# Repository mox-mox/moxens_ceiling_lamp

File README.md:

moxens_ceiling_lamp
===================

This is the source to the lamp that is to light my room

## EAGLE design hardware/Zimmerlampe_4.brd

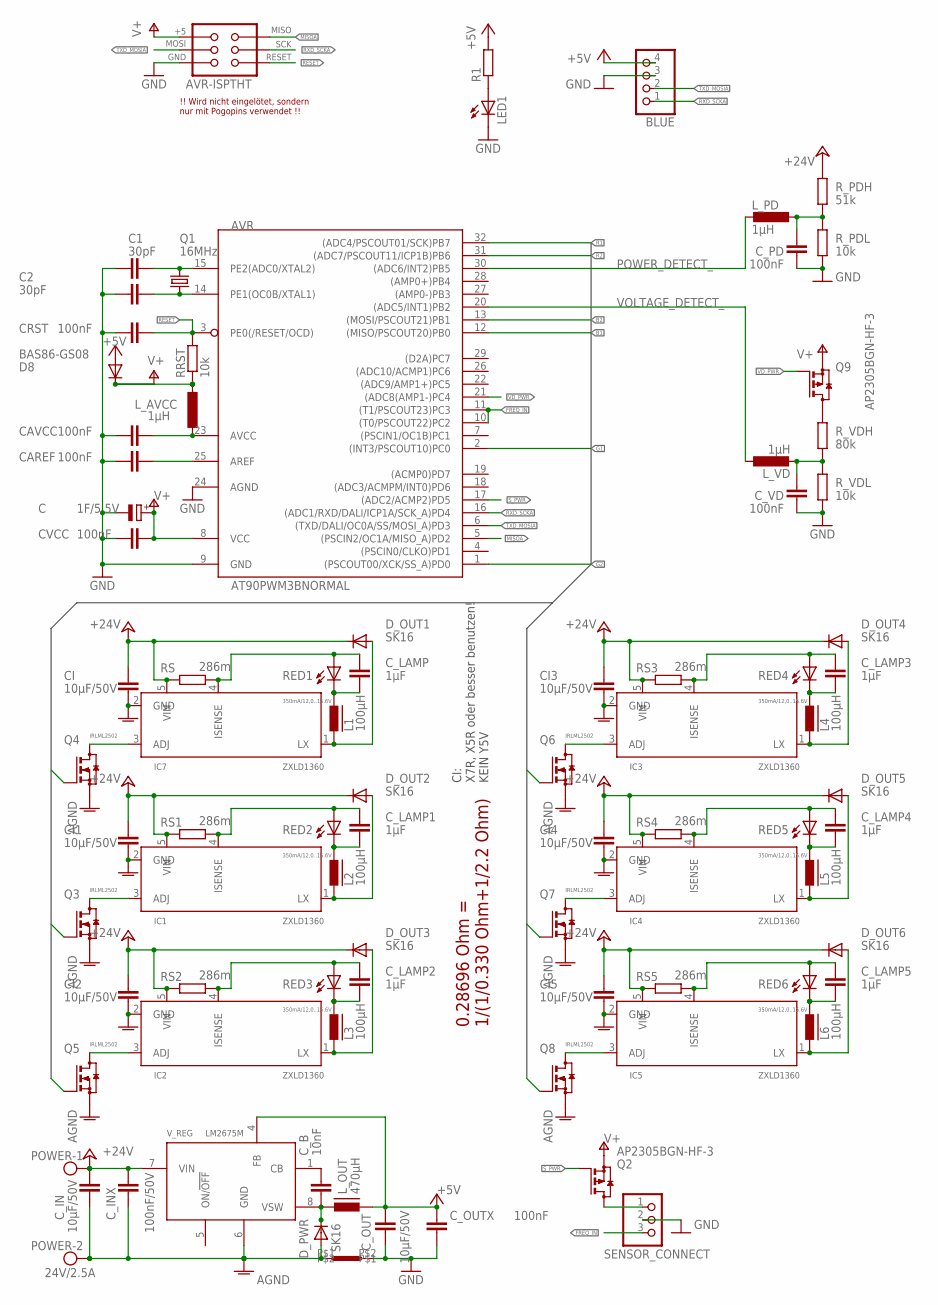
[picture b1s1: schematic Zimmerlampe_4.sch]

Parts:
AVR: AT90PWM3BNORMAL; SO32W
BLUE: PINHD-1X4_2.54-SMD-INLINE; 1X04SMD/INLINE
C: 1F/5.5V; PANASONIC_SG_TERMINAL_H
C1, C2: 30pF; C0805
CAREF: 100nF; C0805
CAVCC: 100nF; C0805
CI, CI1, CI2, CI3, CI4, CI5: 10µF/50V; C1210
CRST: 100nF; C0805
CVCC: 100nF; C0805
C_B: 10nF; C0805
C_IN: 10µF/50V; C1210
C_INX: 100nF/50V; C0805
C_LAMP, C_LAMP1, C_LAMP2, C_LAMP3, C_LAMP4, C_LAMP5: 1µF; C0805
C_OUT: 10µF/50V; C1210
C_OUTX: 100nF; C0805
C_PD: 100nF; C0805
C_VD: 100nF; C0805
D8: BAS86-GS08; MINIMELF
D_OUT1, D_OUT2, D_OUT3, D_OUT4, D_OUT5, D_OUT6: SK16; DO214AA
D_PWR: SK16; DO214AA
IC1, IC2, IC3, IC4, IC5, IC7: ZXLD1360; TSOT23-5
L1, L2, L3, L4, L5, L6: 100µH; FERROCORE_DER0705-
LED1: LEDSML0805; SML0805
L_AVCC: 1µH; L0805
L_OUT: 470µH; FERROCORE_DE1207-
L_PD: 1µH; L0805
L_VD: 1µH; L0805
POWER: 24V/2.5A; AK500/2
Q1: 16MHz; HC49UP
Q2, Q9: AP2305BGN-HF-3; SOT23
Q3, Q4, Q5, Q6, Q7, Q8: IRLML2502; SOT23
R1: R-EU_R0805; R0805
RED1, RED2: 350mA/12,0..15.6V; LED_CON_A
RED3, RED4, RED5, RED6: 350mA/12,0..15.6V; LED_CON_B
RRST: 10k; R0805
RS, RS1, RS2, RS3, RS4, RS5: 286m; R0805
R_PDH: 51k; R0805
R_PDL: 10k; R0805
R_VDH: 80k; R0805
R_VDL: 10k; R0805
SENSOR_CONNECT: 1X03SMD/INLINE
U$3: STARPOINT
U$7: AVR-ISPTHT; AVR-ISP-THT
V_REG: LM2675M; SO08

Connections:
+5V: BLUE.4, C_OUT.1, C_OUTX.1, D8.A, L_OUT.P$2 (2), R1.2, V_REG.4 (FB)
+24V: CI.1, CI1.1, CI2.1, CI3.1, CI4.1, CI5.1, C_IN.1, C_INX.1, D_OUT1.C, D_OUT2.C, D_OUT3.C, D_OUT4.C, D_OUT5.C, D_OUT6.C, IC1.5 (VIN), IC2.5 (VIN), IC3.5 (VIN), IC4.5 (VIN), IC5.5 (VIN), IC7.5 (VIN), POWER.1, RS.1, RS1.1, RS2.1, RS3.1, RS4.1, RS5.1, R_PDH.1, V_REG.7 (VIN)
ADJUST: IC7.3 (ADJ), Q4.3 (D)
ADJUST1: IC1.3 (ADJ), Q3.3 (D)
ADJUST2: IC2.3 (ADJ), Q5.3 (D)
ADJUST3: IC3.3 (ADJ), Q6.3 (D)
ADJUST4: IC4.3 (ADJ), Q7.3 (D)
ADJUST5: IC5.3 (ADJ), Q8.3 (D)
AGND: CI.2, CI1.2, CI2.2, CI3.2, CI4.2, CI5.2, C_IN.2, C_INX.2, D_PWR.A, IC1.2 (GND), IC2.2 (GND), IC3.2 (GND), IC4.2 (GND), IC5.2 (GND), IC7.2 (GND), POWER.2, Q3.2 (S), Q4.2 (S), Q5.2 (S), Q6.2 (S), Q7.2 (S), Q8.2 (S), U$3.P$1, V_REG.6 (GND)
ANODE: C_LAMP.1, IC7.4 (ISENSE), RED1.A, RS.2
ANODE1: C_LAMP1.1, IC1.4 (ISENSE), RED2.A, RS1.2
ANODE2: C_LAMP2.1, IC2.4 (ISENSE), RED3.A, RS2.2
ANODE3: C_LAMP3.1, IC3.4 (ISENSE), RED4.A, RS3.2
ANODE4: C_LAMP4.1, IC4.4 (ISENSE), RED5.A, RS4.2
ANODE5: C_LAMP5.1, IC5.4 (ISENSE), RED6.A, RS5.2
AREF: AVR.25 (AREF), CAREF.2
AVCC: AVR.23 (AVCC), CAVCC.2, L_AVCC.1
B1: AVR.12 ((MISO/PSCOUT20)PB0), Q6.1 (G)
B2: AVR.13 ((MOSI/PSCOUT21)PB1), Q5.1 (G)
CATHODE: C_LAMP.2, L1.P$1 (1), RED1.C
CATHODE1: C_LAMP1.2, L2.P$1 (1), RED2.C
CATHODE2: C_LAMP2.2, L3.P$1 (1), RED3.C
CATHODE3: C_LAMP3.2, L4.P$1 (1), RED4.C
CATHODE4: C_LAMP4.2, L5.P$1 (1), RED5.C
CATHODE5: C_LAMP5.2, L6.P$1 (1), RED6.C
FREEWHEEL: D_OUT1.A, IC7.1 (LX), L1.P$2 (2)
FREEWHEEL1: D_OUT2.A, IC1.1 (LX), L2.P$2 (2)
FREEWHEEL2: D_OUT3.A, IC2.1 (LX), L3.P$2 (2)
FREEWHEEL3: D_OUT4.A, IC3.1 (LX), L4.P$2 (2)
FREEWHEEL4: D_OUT5.A, IC4.1 (LX), L5.P$2 (2)
FREEWHEEL5: D_OUT6.A, IC5.1 (LX), L6.P$2 (2)
FREQ_IN: AVR.10 ((T0/PSCOUT22)PC2), AVR.11 ((T1/PSCOUT23)PC3), SENSOR_CONNECT.3
G1: AVR.2 ((INT3/PSCOUT10)PC0), Q8.1 (G)
G2: AVR.1 ((PSCOUT00/XCK/SS_A)PD0), Q7.1 (G)
GND: AVR.9 (GND), AVR.24 (AGND), BLUE.3, C.-, C1.1, C2.1, CAREF.1, CAVCC.1, CRST.1, CVCC.1, C_OUT.2, C_OUTX.2, C_PD.2, C_VD.2, LED1.C, R_PDL.2, R_VDL.2, SENSOR_CONNECT.2, U$3.P$2, U$7.6 (GND)
MISOA: AVR.5 ((PSCIN2/OC1A/MISO_A)PD2), U$7.1 (MISO)
unnamed: Q9.2 (D), R_VDH.1
unnamed: LED1.A, R1.1
unnamed: C_B.1, V_REG.1 (CB)
POWER_DETECT: C_PD.1, L_PD.1, R_PDH.2, R_PDL.1
POWER_DETECT_: AVR.30 ((ADC6/INT2)PB5), L_PD.2
R1: AVR.32 ((ADC4/PSCOUT01/SCK)PB7), Q3.1 (G)
R2: AVR.31 ((ADC7/PSCOUT11/ICP1B)PB6), Q4.1 (G)
RESET: AVR.3 (PE0(/RESET/OCD)), CRST.2, RRST.2, U$7.5 (RESET)
RXD_SCKA: AVR.16 ((ADC1/RXD/DALI/ICP1A/SCK_A)PD4), BLUE.1, U$7.3 (SCK)
SENSOR_POWER: Q2.2 (D), SENSOR_CONNECT.1
SWITCH: C_B.2, D_PWR.C, L_OUT.P$1 (1), V_REG.8 (VSW)
S_PWR: AVR.17 ((ADC2/ACMP2)PD5), Q2.1 (G)
TXD_MOSIA: AVR.6 ((TXD/DALI/OC0A/SS/MOSI_A)PD3), BLUE.2, U$7.4 (MOSI)
V+: AVR.8 (VCC), C.+, CVCC.2, D8.C, L_AVCC.2, Q2.3 (S), Q9.3 (S), RRST.1, U$7.2 (+5)
VD_PWR: AVR.21 ((ADC8(AMP1-)PC4), Q9.1 (G)
VOLTAGE_DETECT: C_VD.1, L_VD.2, R_VDH.2, R_VDL.1
VOLTAGE_DETECT_: AVR.20 ((ADC5/INT1)PB2), L_VD.1
XTAL1: AVR.14 (PE1(OC0B/XTAL1)), C2.2, Q1.2
XTAL2: AVR.15 (PE2(ADC0/XTAL2)), C1.2, Q1.1

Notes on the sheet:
0.28696 Ohm = 1/(1/0.330 Ohm+1/2.2 Ohm)
!! Wird nicht eingelötet, sondern nur mit Pogopins verwendet !!
CI: X7R, X5R oder besser benutzen! KEIN Y5V

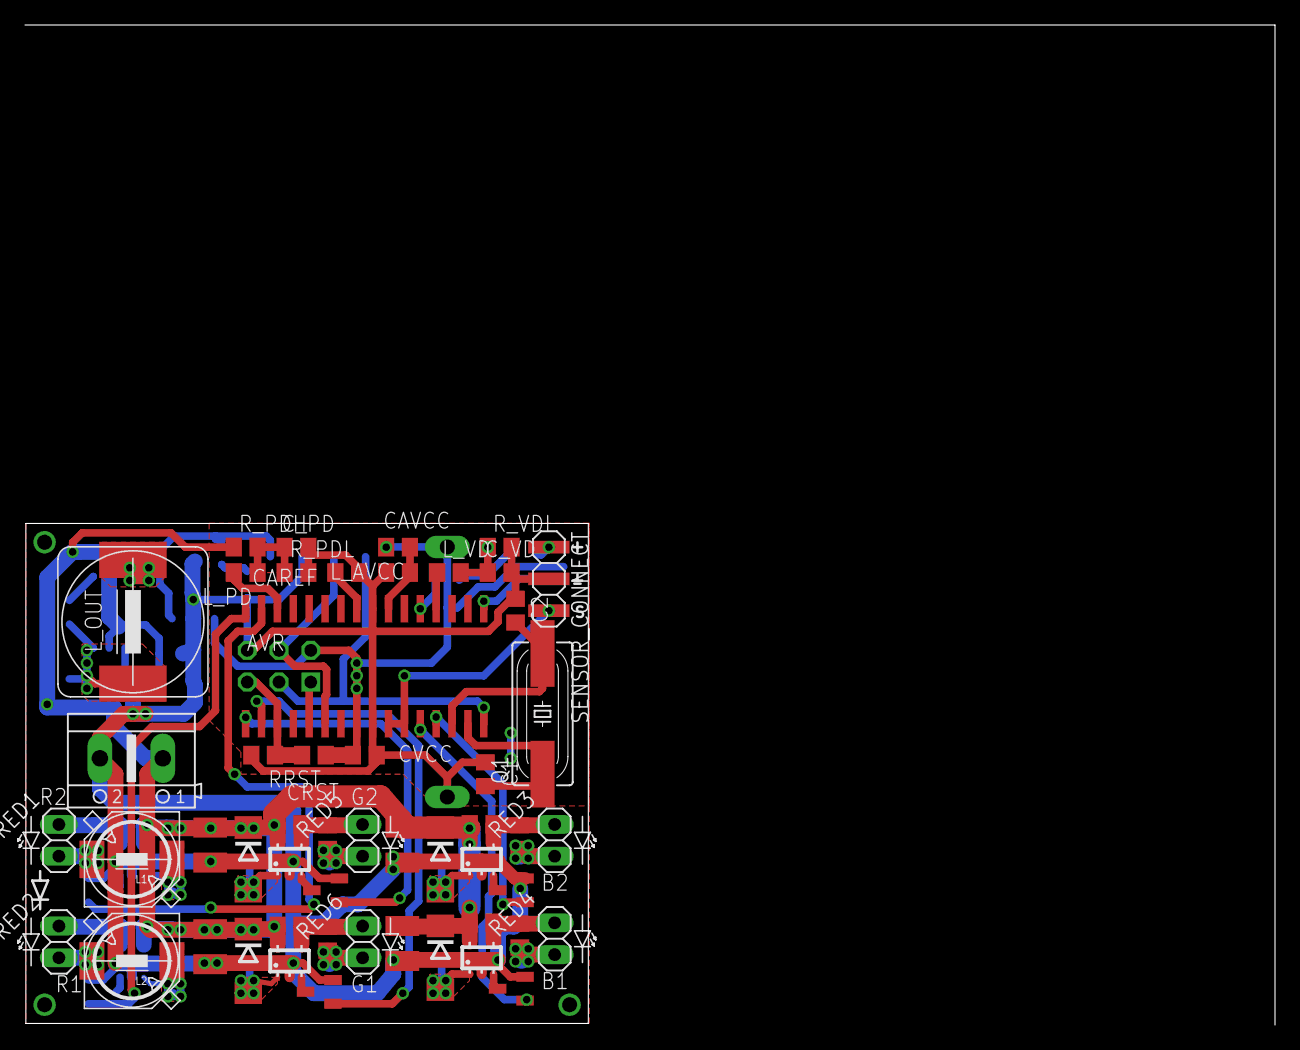
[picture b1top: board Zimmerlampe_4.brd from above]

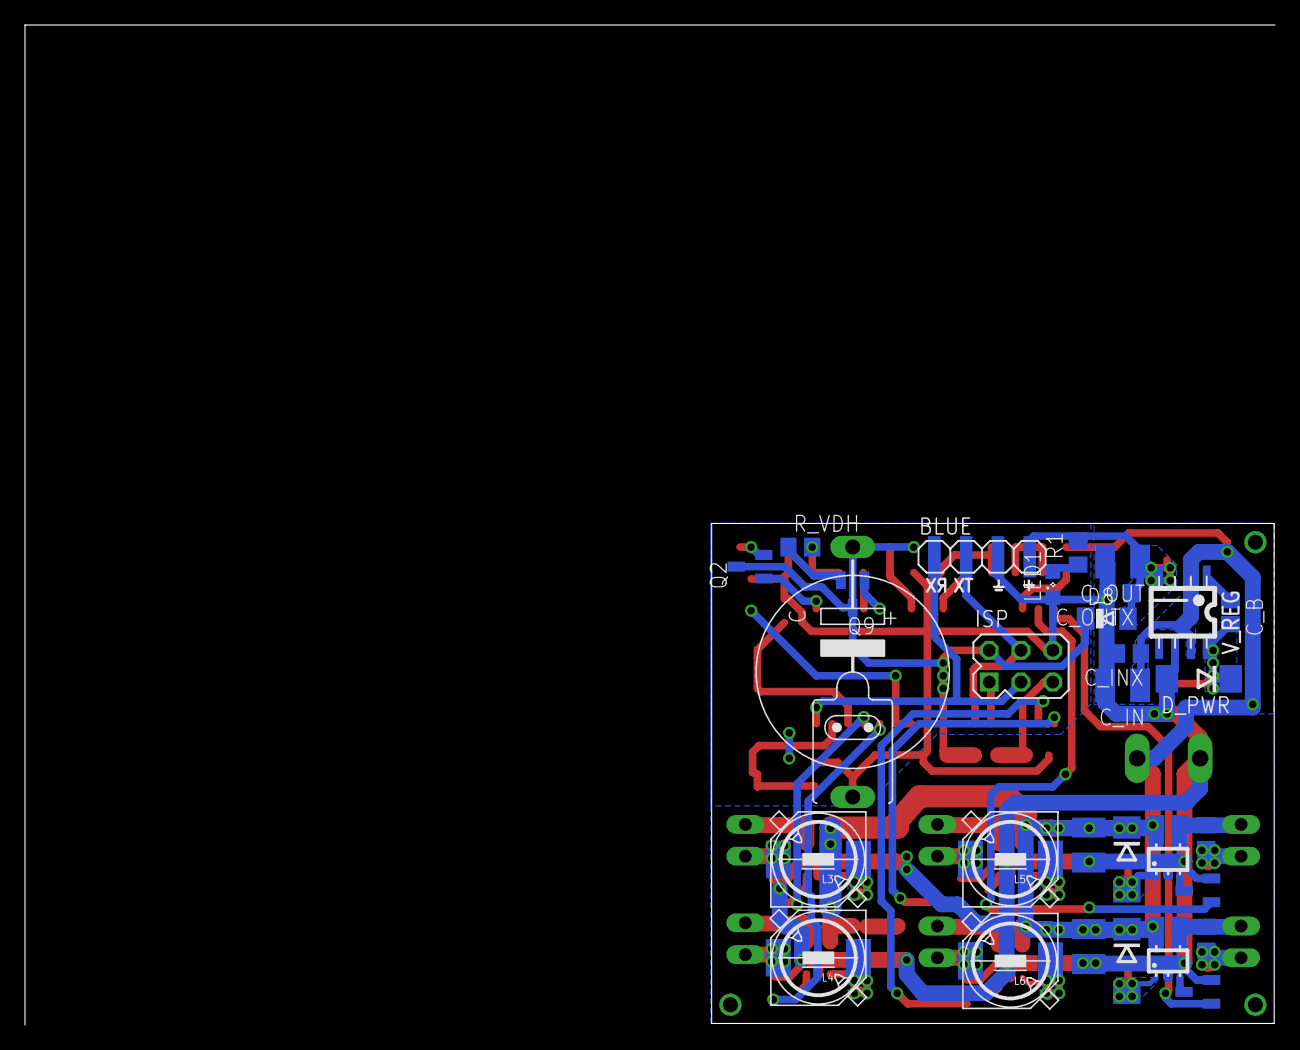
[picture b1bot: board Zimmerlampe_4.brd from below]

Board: 2 copper layers, 45.0 x 40.0 mm, 85 parts (33 on the bottom side), 55 nets.

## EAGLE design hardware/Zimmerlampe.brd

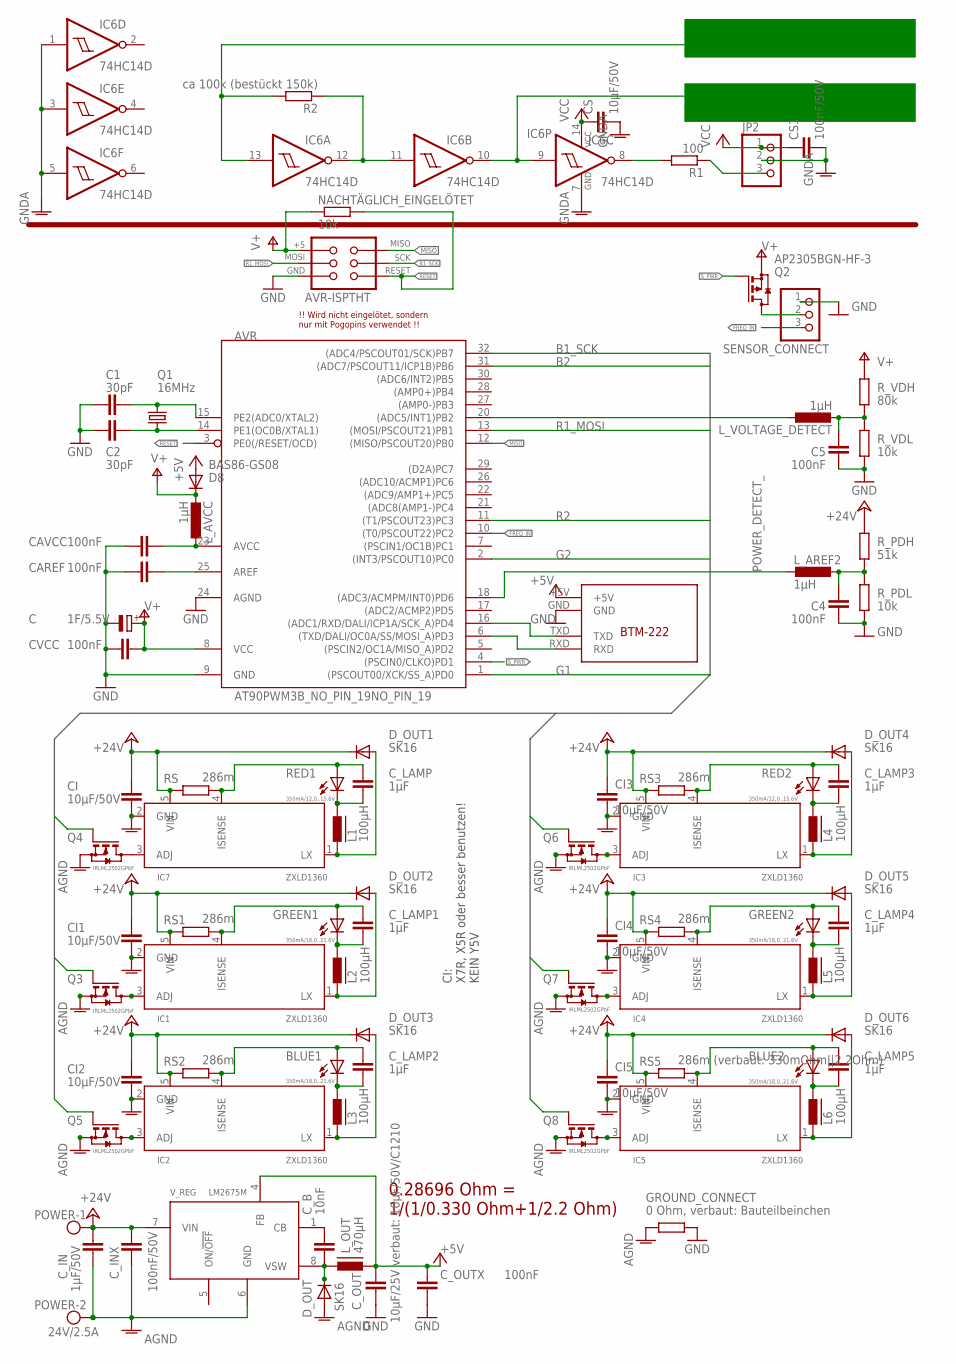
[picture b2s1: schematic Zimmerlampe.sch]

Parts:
AVR: AT90PWM3B_NO_PIN_19NO_PIN_19; SO32W_NO_PIN_19
BLUE1, BLUE2: 350mA/18,0..21.6V; LED5MM
C: 1F/5.5V; PANASONIC_SG_TERMINAL_H
C1, C2: 30pF; C0805
C4, C5: 100nF; C0805
CAREF: 100nF; C0805
CAVCC: 100nF; C0805
CI, CI1, CI2, CI3, CI4, CI5: 10µF/50V; C1210
CS: 10µF/50V; C1210
CS1: 100nF/50V; C0805
CVCC: 100nF; C0805
C_B: 10nF; C0805
C_IN: 1µF/50V; C0805
C_INX: 100nF/50V; C0805
C_LAMP, C_LAMP1, C_LAMP2, C_LAMP3, C_LAMP4, C_LAMP5: 1µF; C0805
C_OUT: 10µF/25V verbaut: 10µF/50V/C1210; C0805
C_OUTX: 100nF; C0805
D8: BAS86-GS08; MINIMELF
D_OUT, D_OUT1, D_OUT2, D_OUT3, D_OUT4, D_OUT5, D_OUT6: SK16; DO214AA
GREEN1, GREEN2: 350mA/18,0..21.6V; LED5MM
GROUND_CONNECT: 0 Ohm, verbaut: Bauteilbeinchen; R0805
IC1, IC2, IC3, IC4, IC5, IC7: ZXLD1360; TSOT23-5
IC6: 74HC14D; SO14
JP2: 1X03SMD/90
L1, L2, L3, L4, L5, L6: 100µH; FERROCORE_DER0705-
L_AREF2: 1µH; L1210
L_AVCC: 1µH; L1210
L_OUT: 470µH; FERROCORE_DE1207-
L_VOLTAGE_DETECT: 1µH; L1210
NACHTÄGLICH_EINGELÖTET: 10k; 0204/7
POWER: 24V/2.5A; AK500/2
Q1: 16MHz; HC49/S
Q2: AP2305BGN-HF-3; SOT23
Q3, Q4, Q5, Q6, Q7, Q8: IRLML2502GPbF; SOT23
R1: 100; R0805
R2: ca 100k (bestückt 150k); R0603
RED1, RED2: 350mA/12,0..15.6V; LED5MM
RS, RS1, RS2, RS3, RS4: 286m; R0805
RS5: 286m (verbaut: 330mOhm||2.2Ohm); R0805
R_PDH: 51k; R0805
R_PDL: 10k; R0805
R_VDH: 80k; R0805
R_VDL: 10k; R0805
SENSOR_CONNECT: 1X03SMD/90
U$1: BTM-222-BASIS; BTM-222
U$7: AVR-ISPTHT; AVR-ISP-THT
V_REG: LM2675M; SO08

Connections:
+5V: C_OUT.1, C_OUTX.1, D8.A, L_OUT.P$2 (2), U$1.+5V, V_REG.4 (FB)
+24V: CI.1, CI1.1, CI2.1, CI3.1, CI4.1, CI5.1, C_IN.1, C_INX.1, D_OUT1.C, D_OUT2.C, D_OUT3.C, D_OUT4.C, D_OUT5.C, D_OUT6.C, IC1.5 (VIN), IC2.5 (VIN), IC3.5 (VIN), IC4.5 (VIN), IC5.5 (VIN), IC7.5 (VIN), POWER.1, RS.1, RS1.1, RS2.1, RS3.1, RS4.1, RS5.1, R_PDH.1, V_REG.7 (VIN)
AGND: CI.2, CI1.2, CI2.2, CI3.2, CI4.2, CI5.2, C_IN.2, C_INX.2, D_OUT.A, GROUND_CONNECT.1, IC1.2 (GND), IC2.2 (GND), IC3.2 (GND), IC4.2 (GND), IC5.2 (GND), IC7.2 (GND), POWER.2, Q3.2 (S), Q4.2 (S), Q5.2 (S), Q6.2 (S), Q7.2 (S), Q8.2 (S), V_REG.6 (GND)
AREF: AVR.25 (AREF), CAREF.2
AVCC: AVR.23 (AVCC), CAVCC.2, L_AVCC.1
B1_SCK: AVR.32 ((ADC4/PSCOUT01/SCK)PB7), Q5.1 (G), U$7.3 (SCK)
B2: AVR.31 ((ADC7/PSCOUT11/ICP1B)PB6), Q8.1 (G)
FREQ_IN: AVR.10 ((T0/PSCOUT22)PC2), SENSOR_CONNECT.3
G1: AVR.1 ((PSCOUT00/XCK/SS_A)PD0), Q3.1 (G)
G2: AVR.2 ((INT3/PSCOUT10)PC0), Q7.1 (G)
GND: AVR.9 (GND), AVR.24 (AGND), C.-, C1.1, C2.1, C4.2, C5.2, CAREF.1, CAVCC.1, CVCC.1, C_OUT.2, C_OUTX.2, GROUND_CONNECT.2, R_PDL.2, R_VDL.2, SENSOR_CONNECT.1, U$1.GND, U$7.6 (GND)
GNDA: CS.2, CS1.2, IC6.1 (I), IC6.3 (I), IC6.5 (I), IC6.7 (GND), JP2.2
MISO: AVR.12 ((MISO/PSCOUT20)PB0), U$7.1 (MISO)
unnamed: AVR.20 ((ADC5/INT1)PB2), L_VOLTAGE_DETECT.1
unnamed: C_LAMP.1, IC7.4 (ISENSE), RED1.A, RS.2
unnamed: C_LAMP.2, L1.P$1 (1), RED1.K (C)
unnamed: D_OUT2.A, IC1.1 (LX), L2.P$2 (2)
unnamed: IC1.3 (ADJ), Q3.3 (D)
unnamed: C_LAMP1.2, GREEN1.K (C), L2.P$1 (1)
unnamed: C_LAMP1.1, GREEN1.A, IC1.4 (ISENSE), RS1.2
unnamed: D_OUT3.A, IC2.1 (LX), L3.P$2 (2)
unnamed: IC2.3 (ADJ), Q5.3 (D)
unnamed: BLUE1.K (C), C_LAMP2.2, L3.P$1 (1)
unnamed: BLUE1.A, C_LAMP2.1, IC2.4 (ISENSE), RS2.2
unnamed: D_OUT4.A, IC3.1 (LX), L4.P$2 (2)
unnamed: IC3.3 (ADJ), Q6.3 (D)
unnamed: C_LAMP3.2, L4.P$1 (1), RED2.K (C)
unnamed: IC7.3 (ADJ), Q4.3 (D)
unnamed: D_OUT1.A, IC7.1 (LX), L1.P$2 (2)
unnamed: C_LAMP3.1, IC3.4 (ISENSE), RED2.A, RS3.2
unnamed: D_OUT5.A, IC4.1 (LX), L5.P$2 (2)
unnamed: IC4.3 (ADJ), Q7.3 (D)
unnamed: C_LAMP4.2, GREEN2.K (C), L5.P$1 (1)
unnamed: C_LAMP4.1, GREEN2.A, IC4.4 (ISENSE), RS4.2
unnamed: D_OUT6.A, IC5.1 (LX), L6.P$2 (2)
unnamed: C_B.1, V_REG.1 (CB)
unnamed: IC5.3 (ADJ), Q8.3 (D)
unnamed: BLUE2.K (C), C_LAMP5.2, L6.P$1 (1)
unnamed: BLUE2.A, C_LAMP5.1, IC5.4 (ISENSE), RS5.2
unnamed: AVR.14 (PE1(OC0B/XTAL1)), C2.2, Q1.2
unnamed: AVR.15 (PE2(ADC0/XTAL2)), C1.2, Q1.1
unnamed: Q2.2 (D), SENSOR_CONNECT.2
unnamed: IC6.13 (I), R2.2
unnamed: IC6.11 (I), IC6.12 (O), R2.1
unnamed: IC6.9 (I), IC6.10 (O)
POWER_DETECT: C4.1, L_AREF2.1, R_PDH.2, R_PDL.1
POWER_DETECT_: AVR.18 ((ADC3/ACMPM/INT0)PD6), L_AREF2.2
R1_MOSI: AVR.13 ((MOSI/PSCOUT21)PB1), Q4.1 (G), U$7.4 (MOSI)
R2: AVR.11 ((T1/PSCOUT23)PC3), Q6.1 (G)
RESET: AVR.3 (PE0(/RESET/OCD)), NACHTÄGLICH_EINGELÖTET.2, U$7.5 (RESET)
RXD: AVR.16 ((ADC1/RXD/DALI/ICP1A/SCK_A)PD4), U$1.TXD
SIG: JP2.3, R1.1
SIG_: IC6.8 (O), R1.2
SWITCH: C_B.2, D_OUT.C, L_OUT.P$1 (1), V_REG.8 (VSW)
S_PWR: AVR.4 ((PSCIN0/CLKO)PD1), Q2.1 (G)
TXD: AVR.6 ((TXD/DALI/OC0A/SS/MOSI_A)PD3), U$1.RXD
V+: AVR.8 (VCC), C.+, CVCC.2, D8.C, L_AVCC.2, NACHTÄGLICH_EINGELÖTET.1, Q2.3 (S), R_VDH.1, U$7.2 (+5)
VCC: CS.1, CS1.1, IC6.14 (VCC), JP2.1
VOLTAGE_DETECT: C5.1, L_VOLTAGE_DETECT.2, R_VDH.2, R_VDL.1

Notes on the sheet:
0.28696 Ohm = 1/(1/0.330 Ohm+1/2.2 Ohm)
!! Wird nicht eingelötet, sondern nur mit Pogopins verwendet !!
CI: X7R, X5R oder besser benutzen! KEIN Y5V

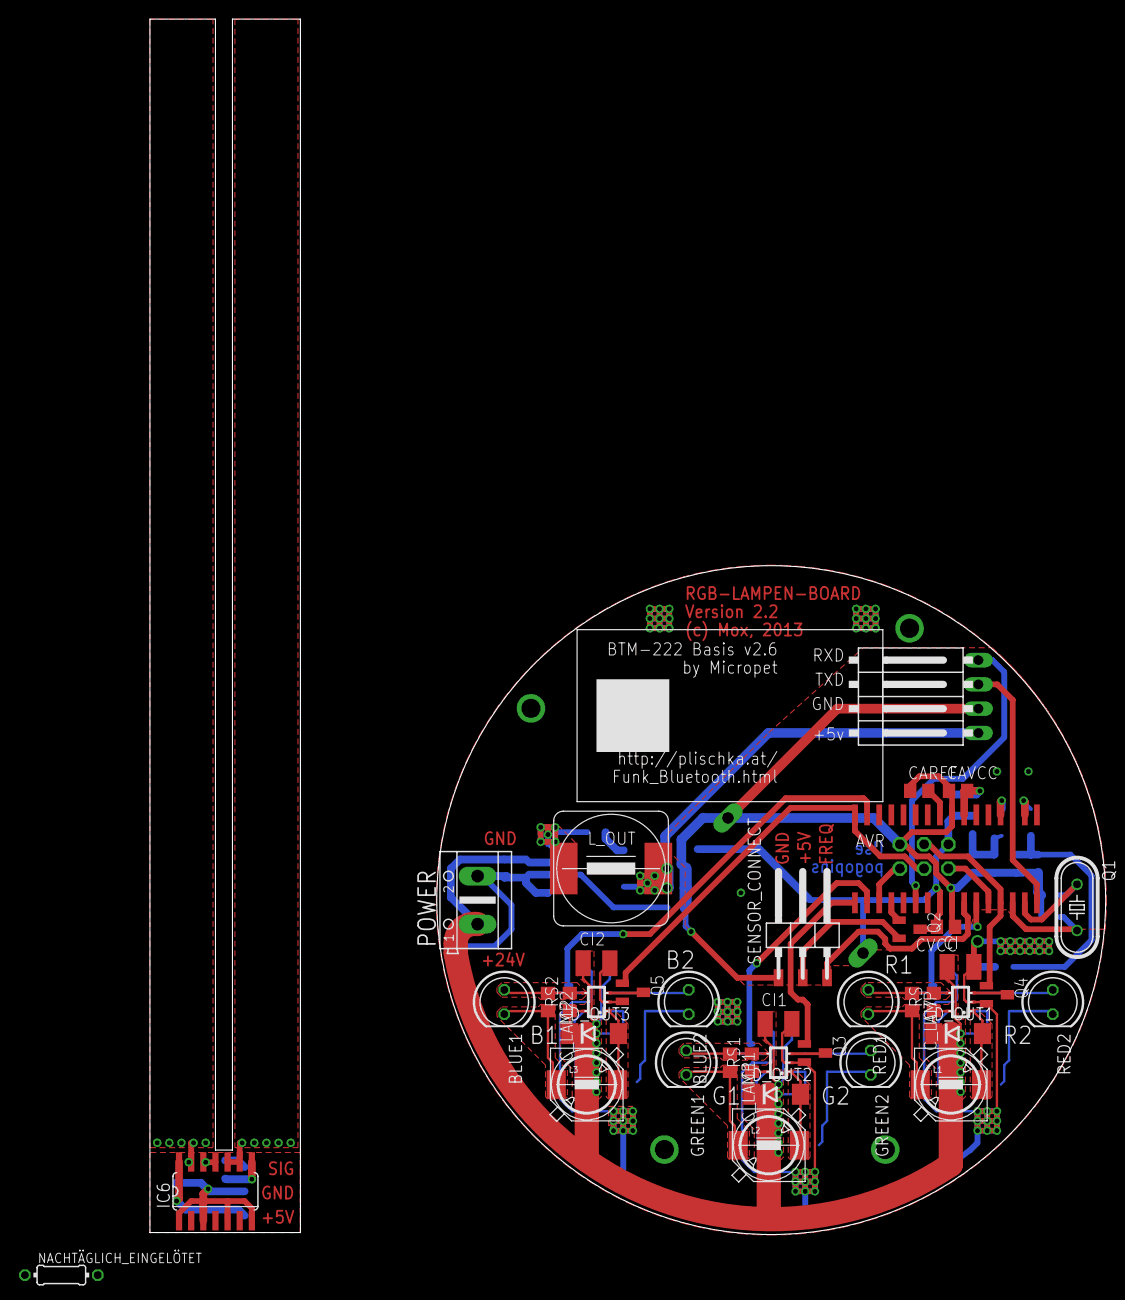
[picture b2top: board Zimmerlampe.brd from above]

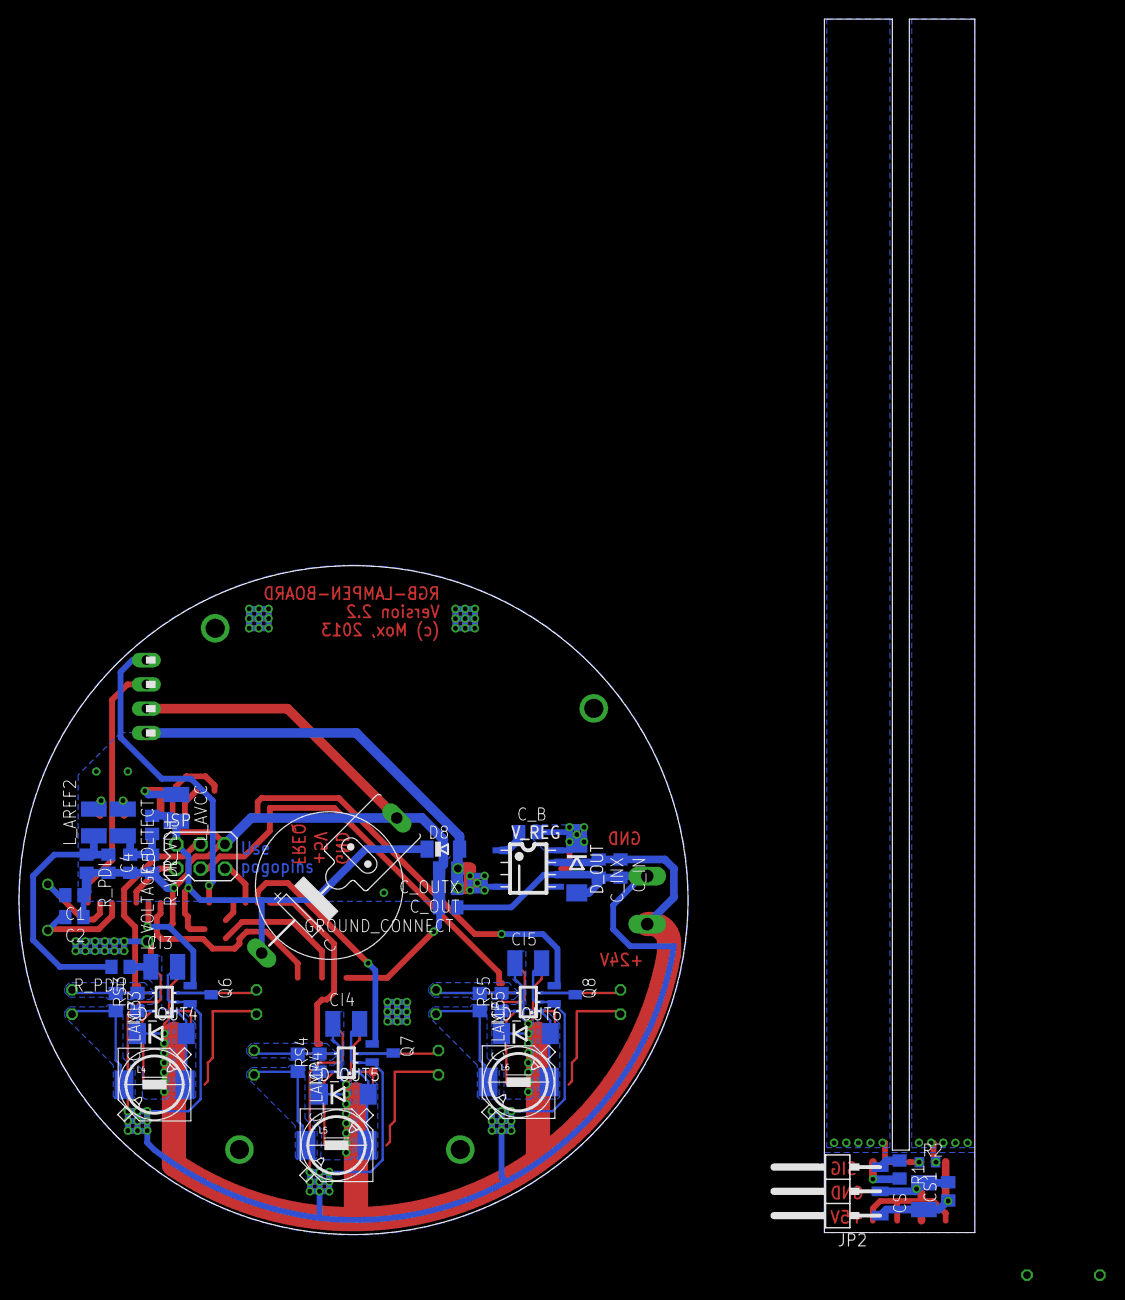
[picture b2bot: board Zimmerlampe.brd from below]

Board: 2 copper layers, 70.0 x 70.0 mm, 87 parts (48 on the bottom side), 59 nets.

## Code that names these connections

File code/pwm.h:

#ifndef PWM_H
#define PWM_H

#define pR1 PB7
#define pG1	PC0
#define pB1 PB0

#define pR2	PB6
#define pG2	PD0
#define pB2	PB1










#endif /* PWM_H */

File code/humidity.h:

#ifndef HUMIDITY_H
#define HUMIDITY_H

#define S_PWR PD5
#define FREQ_IN PC2 // Using T0
//#define FREQ_IN PC3 // Using T1

void get_humidity();
void init_humidity();



#endif /* HUMIDITY_H */

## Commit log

2013-08-22 last commit with cat4101 - They seem to be linear regulators and therefore not suited
2013-08-22 fixed net naming, added Datasheets
2013-08-22 added eagle backup files to gitignore, added eagle.epf
2013-08-23 Switched to ZXLD1360 led driver
2013-08-26 using zxld1360 to drive the leds now, added connection for humidity sensor for the plants
2013-08-27 Final version? Added moisture sensor
2013-08-27 cleared up schematic, replaced pipolar adj-drivers with unipoloar ones, seperated the unused output pins on the sensor from ground
2013-08-27 corrected connections of Q2
2013-08-30 added some values, replaced one diode, moved everything to accomodate bigger cases for the 10µF/50V capacitors
2013-08-31 minor bugfixes
2013-09-05 minor move of the avrs block capacitor
2013-09-07 moved the support capacito® into the middle
2013-09-10 added gnd-pane, improved acces to the 24V for the bottom side led drivers
2013-09-12 resized the gnd-layer on top
2013-09-12 minor improvements
2013-09-12 minor fixes, copied design into sensor board and driver board for ordering
2013-09-12 added identifier field to the layout as needed for ordering with platinensammler
2014-01-29 update and BOM
2014-01-29 changed inductance for connections to the avr to 1µH as bigger ones are not available
2014-02-04 added data for the sensor, started writing some very simple code. Makefile taken for the robotics laboratory of the University of Heidelberg
2014-02-07 ISP connections were wrong. Overhauling and correcting..
2014-02-07 some progress, I might try another layout now..
2014-02-08 wip 2
2014-02-08 minor changes, added ground pane v+
2014-02-08 The design should be finished now, except for the silkscreen which needs more refinement. I will look after this later on
2014-02-09 trying to reduce the space..
2014-02-09 update..
2014-02-09 still a work in progress
2014-02-10 Finished layout of 4th version
2014-02-11 some refinements
2014-02-12 added power led to v+
2014-02-15 foobar
2014-02-15 some small changes and improvements
2014-02-16 started writing the code for the lamp
2014-02-17 sleep time../..
2014-02-17 small update
2014-02-18 very slow progress, but at least some progress
2014-02-19 some updates../..
2014-02-23 changed the width of the polygons to 8 mil
2014-02-23 added 5th version. The drivers are rotated by 180 degrees which is advantageous
2014-02-23 some improvements in the power routing
2014-02-23 Some more improvements in the power routing. Final version?
2014-02-24 Split the connections for T0 and T1, so one can be truncated later. Final version?
2014-02-25 unresolvable bug in version 5, started version6
2014-02-25 redoing everything...
2014-02-26 The power-segment of the board needs to be mirrored, I missed this while layouting :(
2014-02-26 finishing version 6
2014-02-26 adding cool, hopefully final version 6
2014-02-26 moved version 6 to 7 to prepare merging
2014-02-26 final touches to version 6. Version 7 is a dead end.
2014-02-26 Some more improvements
2014-02-26 added overvoltage, overcurrent and reverse voltage protection
2014-02-27 Final Version. Lets hope it works...
2014-02-27 added the ordering file
2014-03-03 started writing some android code
2014-03-03 added path to helpfile to classpath
2014-03-03 Previous commit only seemed to work. Adding the lib instead.
2014-03-04 seems to work more or less
2014-03-04 support/v7 seems to work
2014-03-04 support/v7 did not work, so revert back before it was added
2014-03-06 Rearranged some files
2014-04-04 finished the frequency_meter
2014-04-04 removed the atmel sample for a frequency meter
2014-04-04 nearly done with humidity module, it only the actual sending of the results is left to do
2014-04-06 added psc init
2014-04-06 added most code for the communication
2014-04-06 trying to compile in a minute
2014-04-06 it compiles now../..
2014-04-15 added gradle project skeleton to work up from
2014-04-19 reworked the commands, started writing a command line communicator programm for the pc
2014-04-22 Serial communication (as in 'can echo bytes') is finally working. For some strange reason the cpu frequency is divided by 2.
2014-04-25 corrected off-by-one-error
